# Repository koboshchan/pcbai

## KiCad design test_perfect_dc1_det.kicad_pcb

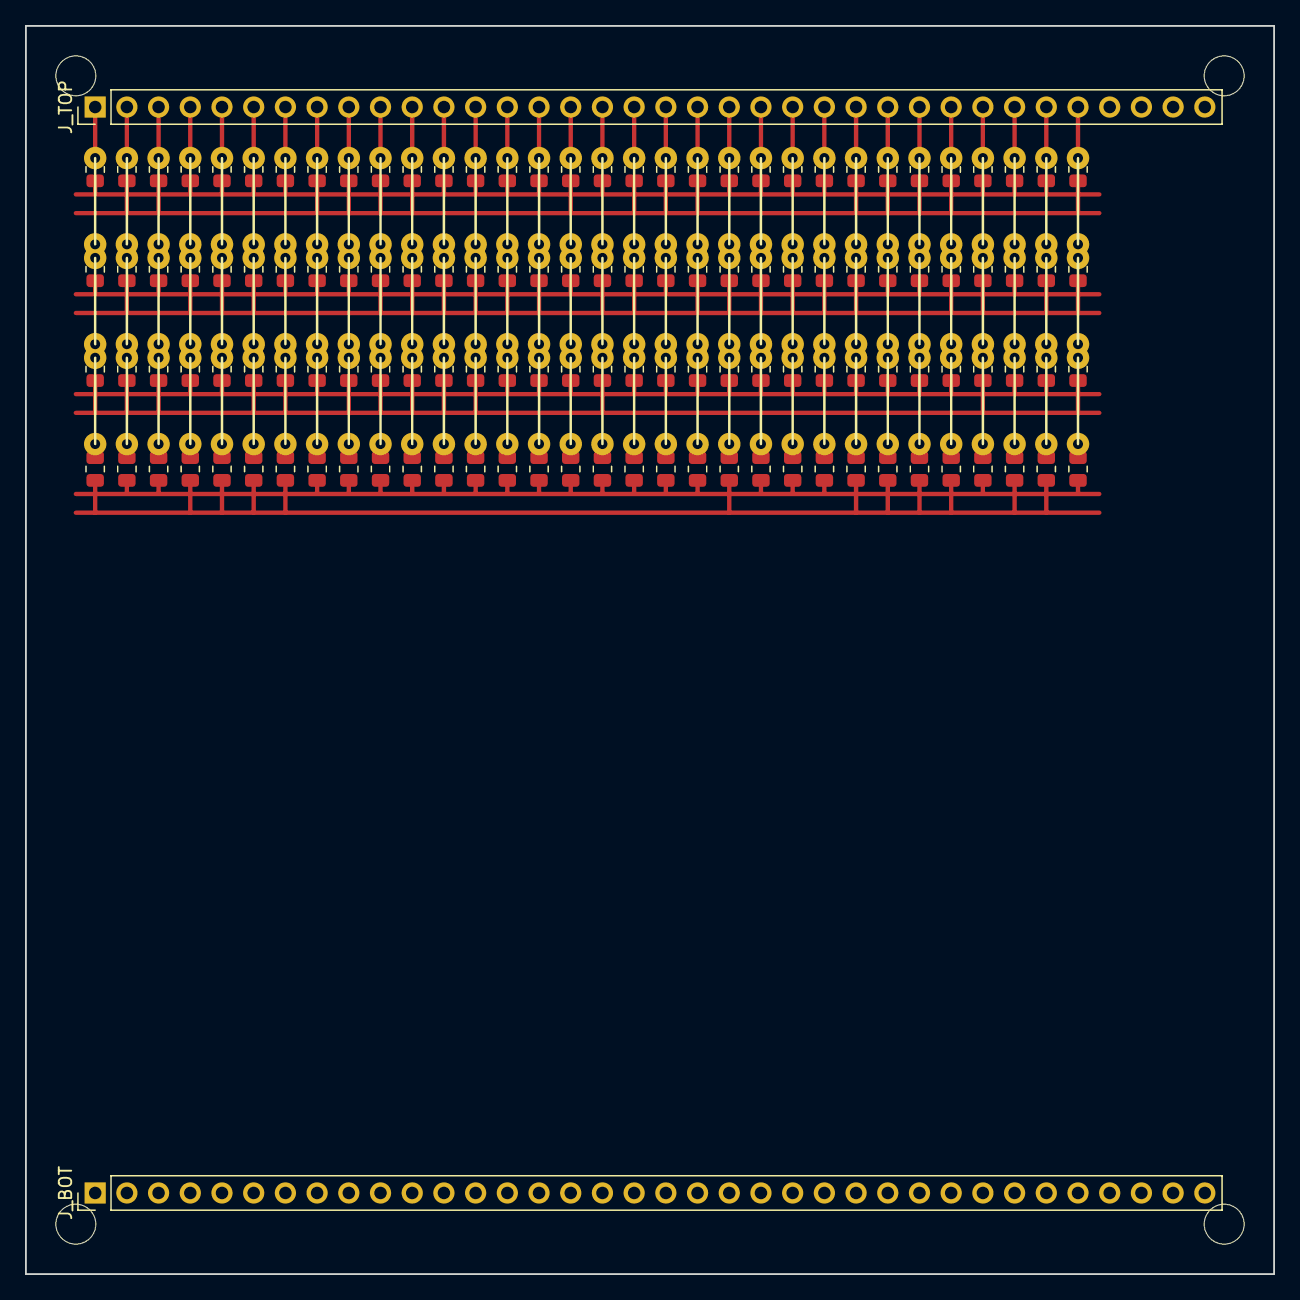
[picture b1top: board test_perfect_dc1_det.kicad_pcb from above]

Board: 2 copper layers, 100.0 x 100.0 mm, 230 parts (0 on the bottom side), 40 nets.

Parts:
J_BOT: INPUTS_32_63_SUM; PinHeader_1x36_P2.54mm_Vertical
J_TOP: INPUTS_0_31_PWR; PinHeader_1x36_P2.54mm_Vertical
MH1, MH2, MH3, MH4: MountingHole_3.2mm_M3
R1_0_0, R1_4_0, R1_7_0, R1_21_0, R1_22_0, R1_26_3, R1_27_0: 12k; R_0805_2012Metric
R1_0_1, R1_3_3, R1_6_1, R1_13_1, R1_14_1, R1_15_0, R1_25_1, R1_27_1: 300k; R_0805_2012Metric
R1_0_2, R1_6_3, R1_11_1, R1_12_1, R1_20_0, R1_30_1: 51k; R_0805_2012Metric
R1_0_3, R1_3_2, R1_11_3, R1_13_2, R1_18_0, R1_27_2: 43k; R_0805_2012Metric
R1_1_0, R1_1_2, R1_7_1, R1_10_0, R1_10_2, R1_16_1, R1_18_1, R1_19_1, R1_20_3, R1_21_3, R1_24_1, R1_28_0, R1_28_3, R1_31_1: 200k; R_0805_2012Metric
R1_1_1, R1_5_3, R1_26_1, R1_31_0: 390k; R_0805_2012Metric
R1_1_3, R1_4_1, R1_5_1, R1_6_0, R1_8_1, R1_10_1, R1_11_0, R1_17_0, R1_22_3, R1_29_3, R1_30_2: 75k; R_0805_2012Metric
R1_2_0, R1_2_2, R1_8_0, R1_8_2, R1_14_2, R1_16_0, R1_18_2, R1_23_3, R1_24_0, R1_26_2, R1_29_0: 22k; R_0805_2012Metric
R1_2_1, R1_2_3, R1_3_0, R1_3_1, R1_9_1, R1_11_2, R1_12_2, R1_12_3, R1_14_3, R1_15_1, R1_17_1, R1_21_1, R1_23_1, R1_28_2, R1_31_3: 100k; R_0805_2012Metric
R1_4_2, R1_4_3, R1_5_0, R1_5_2, R1_9_0, R1_9_3, R1_10_3, R1_13_0, R1_14_0, R1_16_2, R1_17_2, R1_19_2, R1_24_2, R1_25_0, R1_26_0, R1_27_3, R1_30_3: 33k; R_0805_2012Metric
R1_6_2: 680k; R_0805_2012Metric
R1_7_2, R1_15_2, R1_17_3, R1_19_0, R1_21_2, R1_25_3: 10k; R_0805_2012Metric
R1_7_3, R1_9_2, R1_19_3, R1_20_2, R1_30_0: 20k; R_0805_2012Metric
R1_8_3, R1_12_0: 18k; R_0805_2012Metric
R1_13_3, R1_20_1, R1_22_1, R1_28_1, R1_29_1: 1M; R_0805_2012Metric
R1_15_3, R1_18_3, R1_23_0, R1_29_2: 15k; R_0805_2012Metric
R1_16_3, R1_22_2, R1_23_2, R1_24_3, R1_31_2: 7.5k; R_0805_2012Metric
R1_25_2: 47k; R_0805_2012Metric
W1, W2, W3, W4, W5, W6, W7, W8, W9, W10, W11, W12, W13, W14, W15, W16, W17, W18, W19, W20, W21, W22, W23, W24, W25, W26, W27, W28, W29, W30, W31, W32, W33, W34, W35, W36, W37, W38, W39, W40, W41, W42, W43, W44, W45, W46, W47, W48, W49, W50, W51, W52, W53, W54, W55, W56, W57, W58, W59, W60, W61, W62, W63, W64, W65, W66, W67, W68, W69, W70, W71, W72, W73, W74, W75, W76, W77, W78, W79, W80, W81, W82, W83, W84, W85, W86, W87, W88, W89, W90, W91, W92, W93, W94, W95, W96: JUMPER; Jumper_Wire

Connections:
IN_0: J_TOP.1, R1_0_0.1, R1_0_1.1, R1_0_2.1, R1_0_3.1, W1.1, W2.1, W3.1
IN_1: J_TOP.2, R1_1_0.1, R1_1_1.1, R1_1_2.1, R1_1_3.1, W4.1, W5.1, W6.1
IN_2: J_TOP.3, R1_2_0.1, R1_2_1.1, R1_2_2.1, R1_2_3.1, W7.1, W8.1, W9.1
IN_3: J_TOP.4, R1_3_0.1, R1_3_1.1, R1_3_2.1, R1_3_3.1, W10.1, W11.1, W12.1
IN_4: J_TOP.5, R1_4_0.1, R1_4_1.1, R1_4_2.1, R1_4_3.1, W13.1, W14.1, W15.1
IN_5: J_TOP.6, R1_5_0.1, R1_5_1.1, R1_5_2.1, R1_5_3.1, W16.1, W17.1, W18.1
IN_6: J_TOP.7, R1_6_0.1, R1_6_1.1, R1_6_2.1, R1_6_3.1, W19.1, W20.1, W21.1
IN_7: J_TOP.8, R1_7_0.1, R1_7_1.1, R1_7_2.1, R1_7_3.1, W22.1, W23.1, W24.1
IN_8: J_TOP.9, R1_8_0.1, R1_8_1.1, R1_8_2.1, R1_8_3.1, W25.1, W26.1, W27.1
IN_9: J_TOP.10, R1_9_0.1, R1_9_1.1, R1_9_2.1, R1_9_3.1, W28.1, W29.1, W30.1
IN_10: J_TOP.11, R1_10_0.1, R1_10_1.1, R1_10_2.1, R1_10_3.1, W31.1, W32.1, W33.1
IN_11: J_TOP.12, R1_11_0.1, R1_11_1.1, R1_11_2.1, R1_11_3.1, W34.1, W35.1, W36.1
IN_12: J_TOP.13, R1_12_0.1, R1_12_1.1, R1_12_2.1, R1_12_3.1, W37.1, W38.1, W39.1
IN_13: J_TOP.14, R1_13_0.1, R1_13_1.1, R1_13_2.1, R1_13_3.1, W40.1, W41.1, W42.1
IN_14: J_TOP.15, R1_14_0.1, R1_14_1.1, R1_14_2.1, R1_14_3.1, W43.1, W44.1, W45.1
IN_15: J_TOP.16, R1_15_0.1, R1_15_1.1, R1_15_2.1, R1_15_3.1, W46.1, W47.1, W48.1
IN_16: J_TOP.17, R1_16_0.1, R1_16_1.1, R1_16_2.1, R1_16_3.1, W49.1, W50.1, W51.1
IN_17: J_TOP.18, R1_17_0.1, R1_17_1.1, R1_17_2.1, R1_17_3.1, W52.1, W53.1, W54.1
IN_18: J_TOP.19, R1_18_0.1, R1_18_1.1, R1_18_2.1, R1_18_3.1, W55.1, W56.1, W57.1
IN_19: J_TOP.20, R1_19_0.1, R1_19_1.1, R1_19_2.1, R1_19_3.1, W58.1, W59.1, W60.1
IN_20: J_TOP.21, R1_20_0.1, R1_20_1.1, R1_20_2.1, R1_20_3.1, W61.1, W62.1, W63.1
IN_21: J_TOP.22, R1_21_0.1, R1_21_1.1, R1_21_2.1, R1_21_3.1, W64.1, W65.1, W66.1
IN_22: J_TOP.23, R1_22_0.1, R1_22_1.1, R1_22_2.1, R1_22_3.1, W67.1, W68.1, W69.1
IN_23: J_TOP.24, R1_23_0.1, R1_23_1.1, R1_23_2.1, R1_23_3.1, W70.1, W71.1, W72.1
IN_24: J_TOP.25, R1_24_0.1, R1_24_1.1, R1_24_2.1, R1_24_3.1, W73.1, W74.1, W75.1
IN_25: J_TOP.26, R1_25_0.1, R1_25_1.1, R1_25_2.1, R1_25_3.1, W76.1, W77.1, W78.1
IN_26: J_TOP.27, R1_26_0.1, R1_26_1.1, R1_26_2.1, R1_26_3.1, W79.1, W80.1, W81.1
IN_27: J_TOP.28, R1_27_0.1, R1_27_1.1, R1_27_2.1, R1_27_3.1, W82.1, W83.1, W84.1
IN_28: J_TOP.29, R1_28_0.1, R1_28_1.1, R1_28_2.1, R1_28_3.1, W85.1, W86.1, W87.1
IN_29: J_TOP.30, R1_29_0.1, R1_29_1.1, R1_29_2.1, R1_29_3.1, W88.1, W89.1, W90.1
IN_30: J_TOP.31, R1_30_0.1, R1_30_1.1, R1_30_2.1, R1_30_3.1, W91.1, W92.1, W93.1
IN_31: J_TOP.32, R1_31_0.1, R1_31_1.1, R1_31_2.1, R1_31_3.1, W94.1, W95.1, W96.1
SUM_NEG_0: R1_1_0.2, R1_2_0.2, R1_7_0.2, R1_8_0.2, R1_9_0.2, R1_10_0.2, R1_15_0.2, R1_17_0.2, R1_18_0.2, R1_19_0.2, R1_24_0.2, R1_25_0.2, R1_26_0.2, R1_27_0.2, R1_31_0.2
SUM_NEG_1: R1_1_1.2, R1_3_1.2, R1_4_1.2, R1_5_1.2, R1_9_1.2, R1_10_1.2, R1_11_1.2, R1_12_1.2, R1_13_1.2, R1_14_1.2, R1_16_1.2, R1_17_1.2, R1_19_1.2, R1_20_1.2, R1_21_1.2, R1_22_1.2, R1_23_1.2, R1_24_1.2, R1_27_1.2, R1_28_1.2, R1_30_1.2, R1_31_1.2
SUM_NEG_2: R1_0_2.2, R1_1_2.2, R1_2_2.2, R1_5_2.2, R1_6_2.2, R1_8_2.2, R1_9_2.2, R1_10_2.2, R1_11_2.2, R1_12_2.2, R1_16_2.2, R1_28_2.2, R1_31_2.2
SUM_NEG_3: R1_0_3.2, R1_3_3.2, R1_4_3.2, R1_5_3.2, R1_6_3.2, R1_20_3.2, R1_24_3.2, R1_25_3.2, R1_26_3.2, R1_27_3.2, R1_29_3.2, R1_30_3.2
SUM_POS_0: R1_0_0.2, R1_3_0.2, R1_4_0.2, R1_5_0.2, R1_6_0.2, R1_11_0.2, R1_12_0.2, R1_13_0.2, R1_14_0.2, R1_16_0.2, R1_20_0.2, R1_21_0.2, R1_22_0.2, R1_23_0.2, R1_28_0.2, R1_29_0.2, R1_30_0.2
SUM_POS_1: R1_0_1.2, R1_2_1.2, R1_6_1.2, R1_7_1.2, R1_8_1.2, R1_15_1.2, R1_18_1.2, R1_25_1.2, R1_26_1.2, R1_29_1.2
SUM_POS_2: R1_3_2.2, R1_4_2.2, R1_7_2.2, R1_13_2.2, R1_14_2.2, R1_15_2.2, R1_17_2.2, R1_18_2.2, R1_19_2.2, R1_20_2.2, R1_21_2.2, R1_22_2.2, R1_23_2.2, R1_24_2.2, R1_25_2.2, R1_26_2.2, R1_27_2.2, R1_29_2.2, R1_30_2.2
SUM_POS_3: R1_1_3.2, R1_2_3.2, R1_7_3.2, R1_8_3.2, R1_9_3.2, R1_10_3.2, R1_11_3.2, R1_12_3.2, R1_13_3.2, R1_14_3.2, R1_15_3.2, R1_16_3.2, R1_17_3.2, R1_18_3.2, R1_19_3.2, R1_21_3.2, R1_22_3.2, R1_23_3.2, R1_28_3.2, R1_31_3.2

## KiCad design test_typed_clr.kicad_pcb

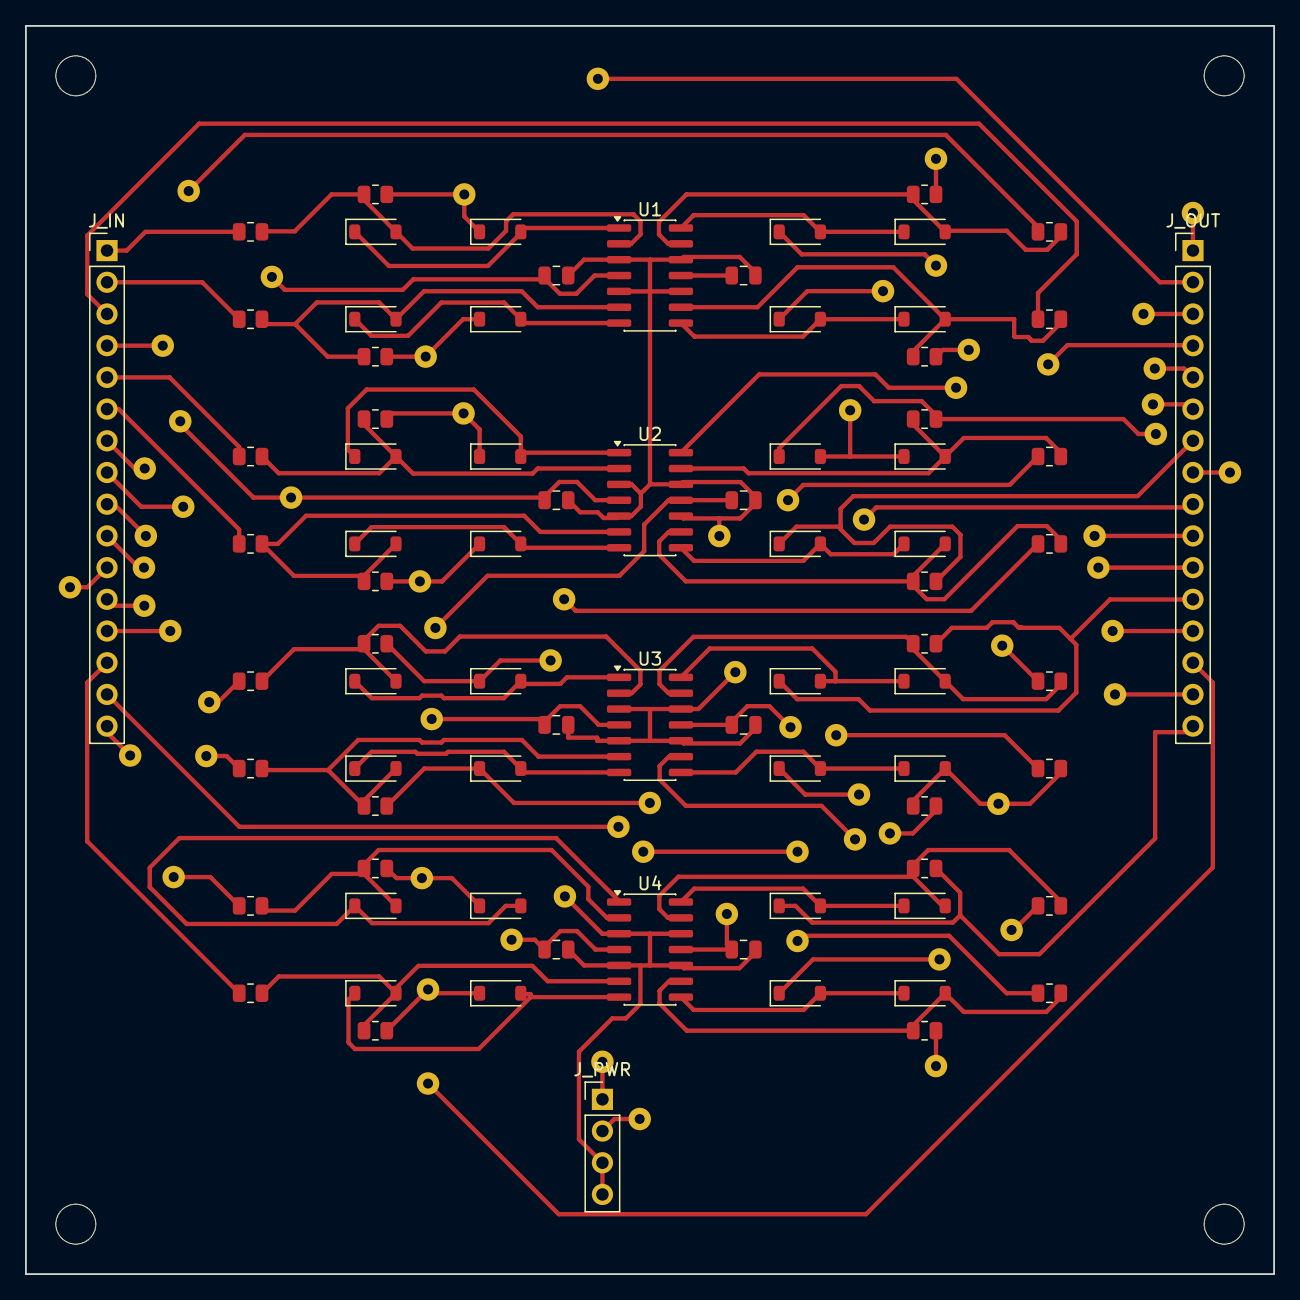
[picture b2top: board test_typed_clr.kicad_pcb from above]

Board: 2 copper layers, 100.0 x 100.0 mm, 113 parts (0 on the bottom side), 67 nets.

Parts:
C_1_NEG, C_1_POS, C_2_NEG, C_2_POS, C_3_NEG, C_3_POS, C_4_NEG, C_4_POS: 100n; C_0805_2012Metric
D_FB_0, D_FB_1, D_FB_2, D_FB_3, D_FB_4, D_FB_5, D_FB_6, D_FB_7, D_FB_8, D_FB_9, D_FB_10, D_FB_11, D_FB_12, D_FB_13, D_FB_14, D_FB_15: 1N4148; D_SOD-123
D_OUT_0, D_OUT_1, D_OUT_2, D_OUT_3, D_OUT_4, D_OUT_5, D_OUT_6, D_OUT_7, D_OUT_8, D_OUT_9, D_OUT_10, D_OUT_11, D_OUT_12, D_OUT_13, D_OUT_14, D_OUT_15: 1N4148; D_SOD-123
J_IN: V_SUM_IN; PinHeader_1x16_P2.54mm_Vertical
J_OUT: ACT_OUT; PinHeader_1x16_P2.54mm_Vertical
J_PWR: POWER; PinHeader_1x04_P2.54mm_Vertical
MH1, MH2, MH3, MH4: MountingHole_3.2mm_M3
R_FB_0, R_FB_1, R_FB_2, R_FB_3, R_FB_4, R_FB_5, R_FB_6, R_FB_7, R_FB_8, R_FB_9, R_FB_10, R_FB_11, R_FB_12, R_FB_13, R_FB_14, R_FB_15: 10k; R_0805_2012Metric
R_IN_0, R_IN_1, R_IN_2, R_IN_3, R_IN_4, R_IN_5, R_IN_6, R_IN_7, R_IN_8, R_IN_9, R_IN_10, R_IN_11, R_IN_12, R_IN_13, R_IN_14, R_IN_15: 10k; R_0805_2012Metric
U1, U2, U3, U4: TL074; SOIC-14_3.9x8.7mm_P1.27mm
W1, W2, W3, W4, W5, W6, W7, W8, W9, W10, W11, W12, W13, W14, W15, W16, W17, W18, W19, W20, W21, W22, W23, W24, W25, W26, W27, W28, W29, W30: JUMPER

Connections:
+12V: C_1_POS.1, C_2_POS.1, C_3_POS.1, C_4_POS.1, J_PWR.1, U1.4, U2.4, U3.4, U4.4, W27.1, W28.1
-12V: C_1_NEG.1, C_2_NEG.1, C_3_NEG.1, C_4_NEG.1, J_PWR.2, U1.11, U2.11, U3.11, U4.11, W26.1
ACT_0: D_OUT_0.1, J_OUT.1, R_FB_0.2, W30.1
ACT_1: D_OUT_1.1, J_OUT.2, R_FB_1.2, W21.1
ACT_2: D_OUT_2.1, J_OUT.3, R_FB_2.2, W20.1
ACT_3: D_OUT_3.1, J_OUT.4, R_FB_3.2, W24.1
ACT_4: D_OUT_4.1, J_OUT.5, R_FB_4.2, W19.1
ACT_5: D_OUT_5.1, J_OUT.6, R_FB_5.2, W18.1
ACT_6: D_OUT_6.1, J_OUT.7, R_FB_6.2
ACT_7: D_OUT_7.1, J_OUT.8, R_FB_7.2, W17.1
ACT_8: D_OUT_8.1, J_OUT.9, R_FB_8.2, W16.1
ACT_9: D_OUT_9.1, J_OUT.10, R_FB_9.2, W15.1
ACT_10: D_OUT_10.1, J_OUT.11, R_FB_10.2, W14.1
ACT_11: D_OUT_11.1, J_OUT.12, R_FB_11.2
ACT_12: D_OUT_12.1, J_OUT.13, R_FB_12.2, W25.1
ACT_13: D_OUT_13.1, J_OUT.14, R_FB_13.2, W13.1
ACT_14: D_OUT_14.1, J_OUT.15, R_FB_14.2, W12.1
ACT_15: D_OUT_15.1, J_OUT.16, R_FB_15.2
GND: C_1_NEG.2, C_1_POS.2, C_2_NEG.2, C_2_POS.2, C_3_NEG.2, C_3_POS.2, C_4_NEG.2, C_4_POS.2, J_PWR.3, J_PWR.4, U1.3, U1.5, U1.10, U1.12, U2.3, U2.5, U2.10, U2.12, U3.3, U3.5, U3.10, U3.12, U4.3, U4.5, U4.10, U4.12, W29.1
INV_IN_0: D_FB_0.2, R_FB_0.1, R_IN_0.2, U1.2
INV_IN_1: D_FB_1.2, R_FB_1.1, R_IN_1.2, U1.6
INV_IN_2: D_FB_2.2, R_FB_2.1, R_IN_2.2, U1.9
INV_IN_3: D_FB_3.2, R_FB_3.1, R_IN_3.2, U1.13
INV_IN_4: D_FB_4.2, R_FB_4.1, R_IN_4.2, U2.2
INV_IN_5: D_FB_5.2, R_FB_5.1, R_IN_5.2, U2.6
INV_IN_6: D_FB_6.2, R_FB_6.1, R_IN_6.2, U2.9
INV_IN_7: D_FB_7.2, R_FB_7.1, R_IN_7.2, U2.13
INV_IN_8: D_FB_8.2, R_FB_8.1, R_IN_8.2, U3.2
INV_IN_9: D_FB_9.2, R_FB_9.1, R_IN_9.2, U3.6
INV_IN_10: D_FB_10.2, R_FB_10.1, R_IN_10.2, U3.9, W7.1
INV_IN_11: D_FB_11.2, R_FB_11.1, R_IN_11.2, U3.13
INV_IN_12: D_FB_12.2, R_FB_12.1, R_IN_12.2, U4.2
INV_IN_13: D_FB_13.2, R_FB_13.1, R_IN_13.2, U4.6
INV_IN_14: D_FB_14.2, R_FB_14.1, R_IN_14.2, U4.9
INV_IN_15: D_FB_15.2, R_FB_15.1, R_IN_15.2, U4.13
OP_OUT_0: D_FB_0.1, D_OUT_0.2, U1.1
OP_OUT_1: D_FB_1.1, D_OUT_1.2, U1.7
OP_OUT_2: D_FB_2.1, D_OUT_2.2, U1.8
OP_OUT_3: D_FB_3.1, D_OUT_3.2, U1.14
OP_OUT_4: D_FB_4.1, D_OUT_4.2, U2.1
OP_OUT_5: D_FB_5.1, D_OUT_5.2, U2.7
OP_OUT_6: D_FB_6.1, D_OUT_6.2, U2.8
OP_OUT_7: D_FB_7.1, D_OUT_7.2, U2.14, W22.1
OP_OUT_8: D_FB_8.1, D_OUT_8.2, U3.1
OP_OUT_9: D_FB_9.1, D_OUT_9.2, U3.7
OP_OUT_10: D_FB_10.1, D_OUT_10.2, U3.8
OP_OUT_11: D_FB_11.1, D_OUT_11.2, U3.14
OP_OUT_12: D_FB_12.1, D_OUT_12.2, U4.1
OP_OUT_13: D_FB_13.1, D_OUT_13.2, U4.7
OP_OUT_14: D_FB_14.1, D_OUT_14.2, U4.8
OP_OUT_15: D_FB_15.1, D_OUT_15.2, U4.14
V_SUM_0: J_IN.1, R_IN_0.1
V_SUM_1: J_IN.2, R_IN_1.1
V_SUM_2: J_IN.3, R_IN_2.1
V_SUM_3: J_IN.4, R_IN_3.1, W23.1
V_SUM_4: J_IN.5, R_IN_4.1
V_SUM_5: J_IN.6, R_IN_5.1
V_SUM_6: J_IN.7, R_IN_6.1, W10.1
V_SUM_7: J_IN.8, R_IN_7.1, W6.1
V_SUM_8: J_IN.9, R_IN_8.1, W5.1
V_SUM_9: J_IN.10, R_IN_9.1, W4.1
V_SUM_10: J_IN.11, R_IN_10.1, W3.1
V_SUM_11: J_IN.12, R_IN_11.1, W2.1
V_SUM_12: J_IN.13, R_IN_12.1, W1.1
V_SUM_13: J_IN.14, R_IN_13.1
V_SUM_14: J_IN.15, R_IN_14.1, W8.1, W9.1
V_SUM_15: J_IN.16, R_IN_15.1, W11.1

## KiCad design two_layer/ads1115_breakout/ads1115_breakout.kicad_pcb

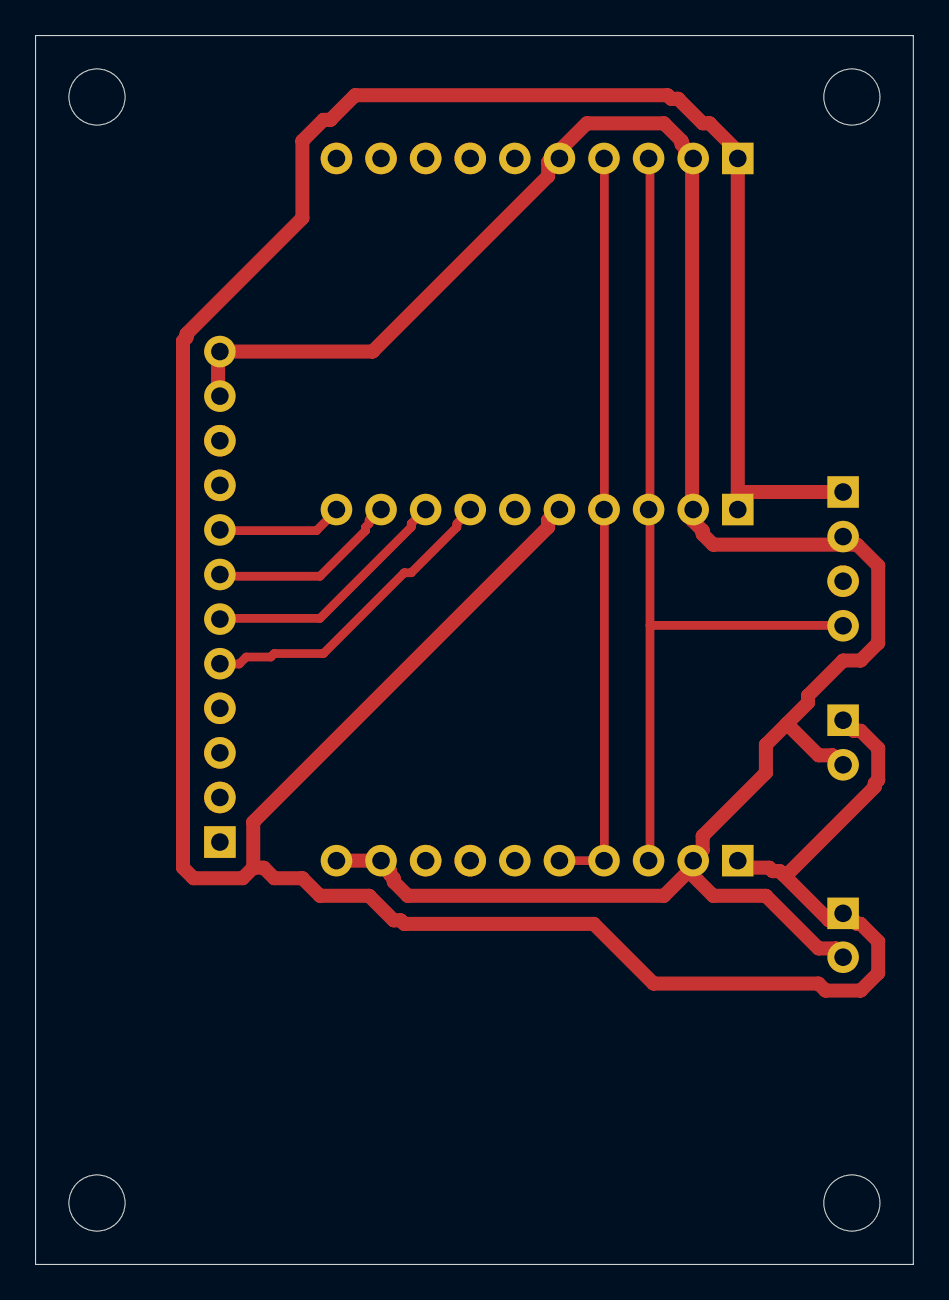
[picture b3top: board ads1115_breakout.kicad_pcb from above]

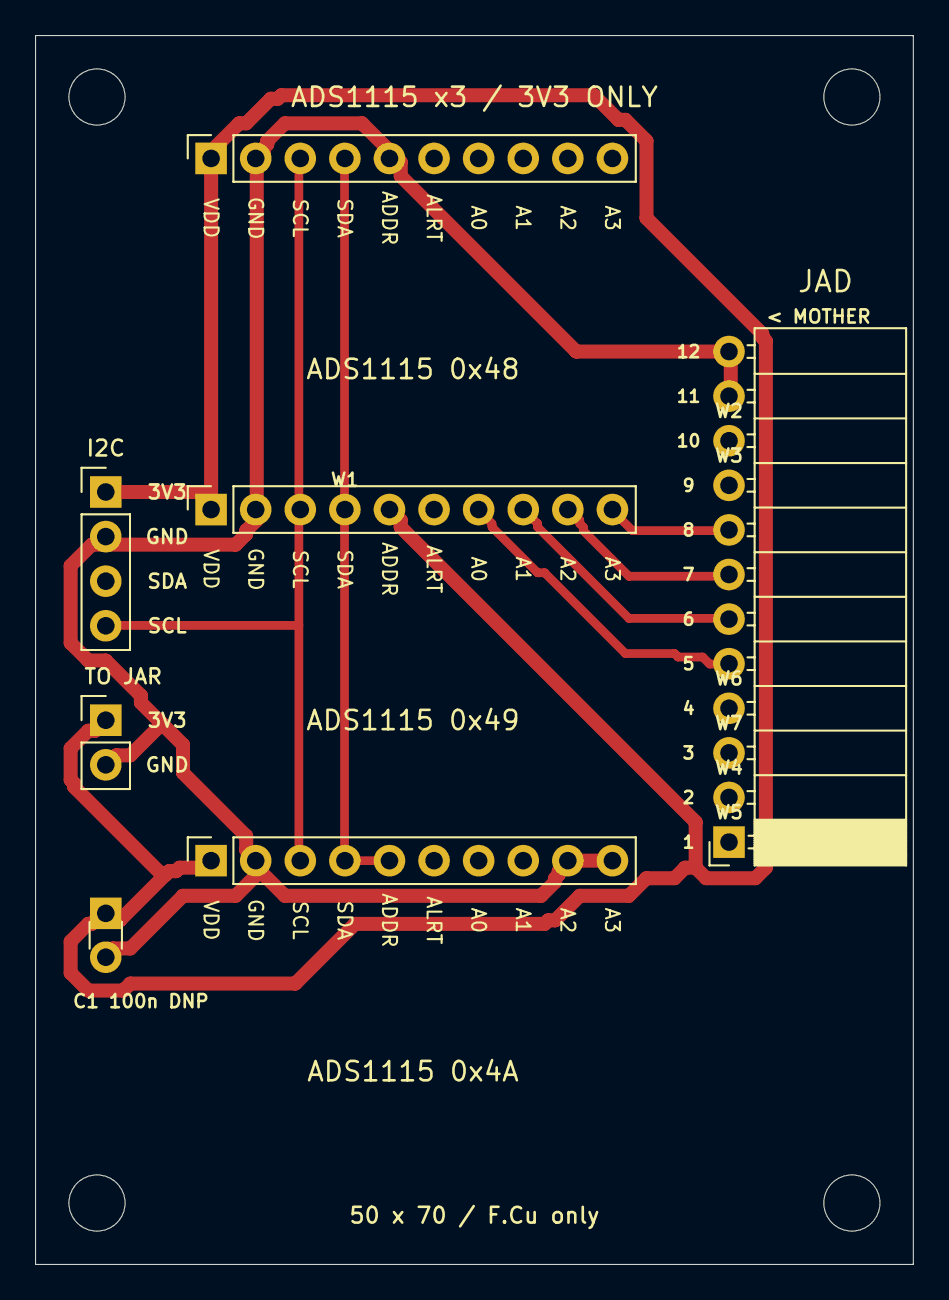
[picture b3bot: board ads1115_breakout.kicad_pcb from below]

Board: 2 copper layers, 50.0 x 70.0 mm, 18 parts (7 on the bottom side), 14 nets.

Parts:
C1: C_Disc_D3.0mm_W1.6mm_P2.50mm
H1, H2, H3, H4: MountingHole_3.2mm_M3
JAD: PinSocket_1x12_P2.54mm_Horizontal
JAR: PinHeader_1x02_P2.54mm_Vertical
JI2C: PinHeader_1x04_P2.54mm_Vertical
JM1, JM2, JM3: PinSocket_1x10_P2.54mm_Vertical
W1: SDA insulated wire
W2: ADC_9 insulated wire
W3: ADC_8 insulated wire
W4: ADC_1 insulated wire
W5: ADC_0 insulated wire
W6: ADC_3 insulated wire
W7: ADC_2 insulated wire

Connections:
3V3: C1.1, JAR.1, JI2C.1, JM1.1, JM2.1, JM2.5, JM3.1
ADC_0: JAD.1, JM1.7, W5.1
ADC_1: JAD.2, JM1.8, W4.1
ADC_2: JAD.3, JM1.9, W7.1
ADC_3: JAD.4, JM1.10, W6.1
ADC_4: JAD.5, JM2.7
ADC_5: JAD.6, JM2.8
ADC_6: JAD.7, JM2.9
ADC_7: JAD.8, JM2.10
ADC_8: JAD.9, JM3.7, W3.1
ADC_9: JAD.10, JM3.8, W2.1
GND: C1.2, JAD.11, JAD.12, JAR.2, JI2C.2, JM1.2, JM1.5, JM2.2, JM3.2, JM3.9, JM3.10
SCL: JI2C.4, JM1.3, JM2.3, JM3.3
SDA: JI2C.3, JM1.4, JM2.4, JM3.4, JM3.5, W1.1

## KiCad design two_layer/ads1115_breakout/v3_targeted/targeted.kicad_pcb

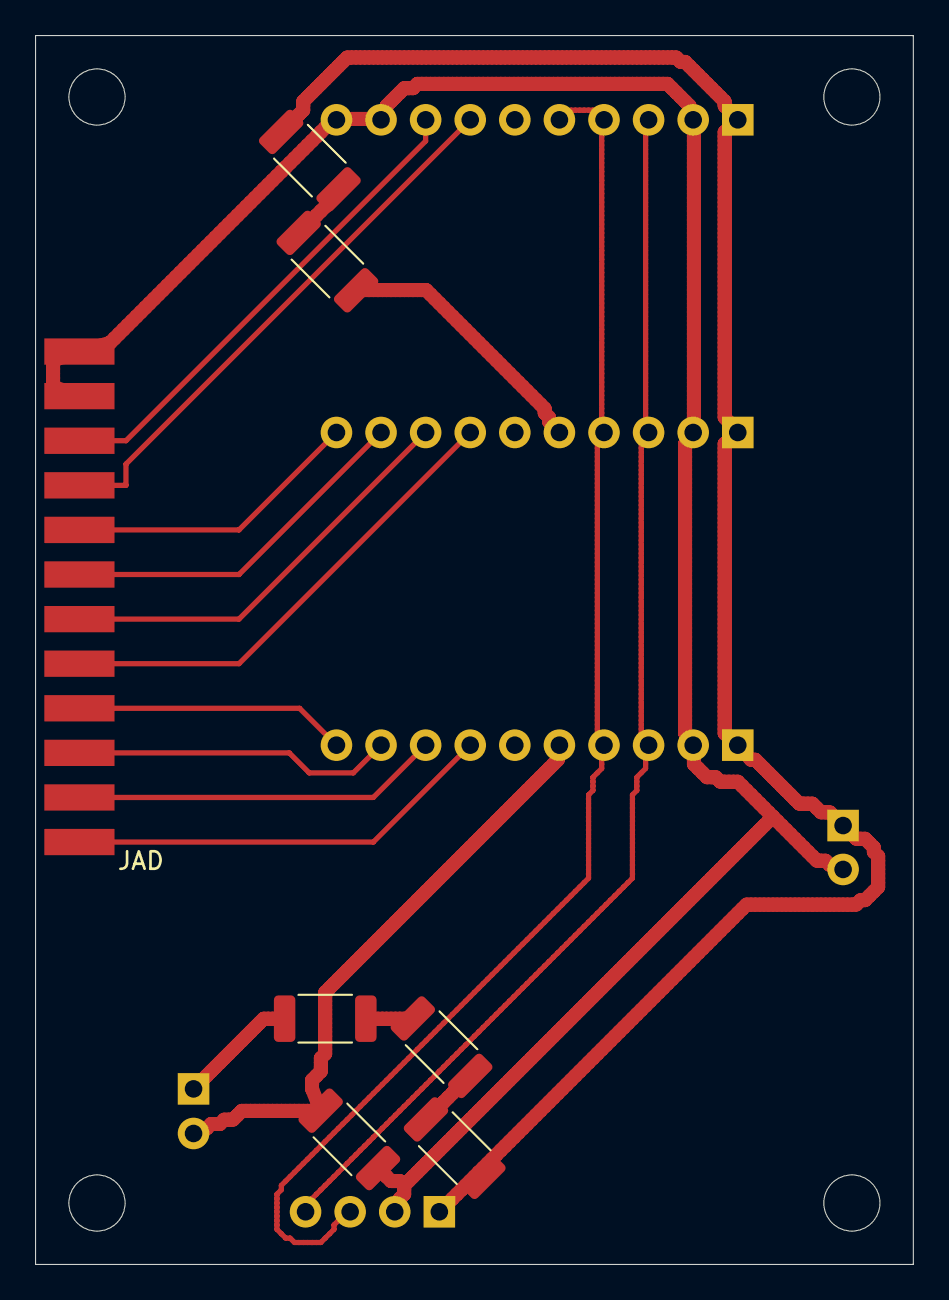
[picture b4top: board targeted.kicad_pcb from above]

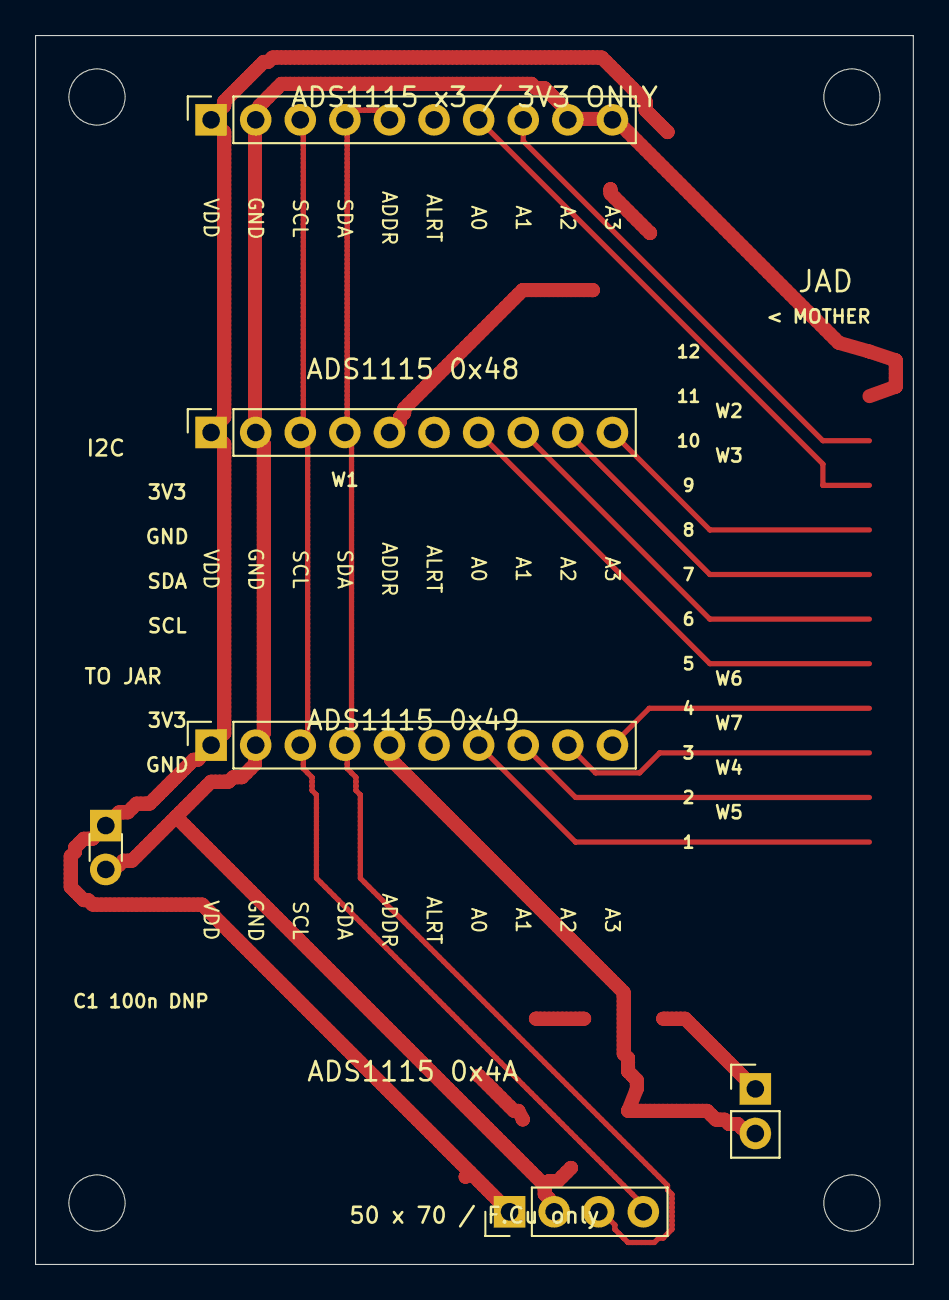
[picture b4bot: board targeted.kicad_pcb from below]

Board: 2 copper layers, 50.0 x 70.0 mm, 17 parts (6 on the bottom side), 20 nets.

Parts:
C1: C_Disc_D3.0mm_W1.6mm_P2.50mm
H1, H2, H3, H4: MountingHole_3.2mm_M3
JAD: Custom_1x12_Male_Edge_FCu_NOMINAL; MaleEdge_1x12_P2.54_OneFace
JAR: PinHeader_1x02_P2.54mm_Vertical
JI2C: PinHeader_1x04_P2.54mm_Vertical
JM1, JM2, JM3: PinSocket_1x10_P2.54mm_Vertical
R1, R2, R3, R4, R5, R6: 0R; R_2010_5025Metric

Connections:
3V3: R2.1, R3.2
3V3_JT1: R3.1, R4.2
3V3_JT2: C1.1, JI2C.1, JM1.1, JM2.1, JM3.1, R2.2, R5.1
3V3_JT3: JAR.1, R4.1
3V3_JT4: JM2.5, R6.2
3V3_JT5: R5.2, R6.1
ADC_0: JAD.1, JM1.7
ADC_1: JAD.2, JM1.8
ADC_2: JAD.3, JM1.9
ADC_3: JAD.4, JM1.10
ADC_4: JAD.5, JM2.7
ADC_5: JAD.6, JM2.8
ADC_6: JAD.7, JM2.9
ADC_7: JAD.8, JM2.10
ADC_8: JAD.9, JM3.7
ADC_9: JAD.10, JM3.8
GND: C1.2, JAD.11, JAD.12, JI2C.2, JM1.2, JM2.2, JM3.2, JM3.9, JM3.10, R1.2
GND_JT1: JAR.2, JM1.5, R1.1
SCL: JI2C.4, JM1.3, JM2.3, JM3.3
SDA: JI2C.3, JM1.4, JM2.4, JM3.4, JM3.5
